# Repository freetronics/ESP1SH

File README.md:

Freetronics ESP8266 / ESP-01 (WiFi) Breakout Shield
===================================================
Copyright 2014-2017 Freetronics Pty Ltd www.freetronics.com  

A shield for the Arduino and other microcontroller boards based on the
same header format, such as the Freetronics Eleven. Includes a header
to mount an ESP-01 module containing an ESP8266 WiFi chipset and
supporting parts, giving your Arduino WiFi capabilities.

Includes level shifters to allow safe operation on both 3.3V and 5V
Arduino boards.

More information is available on our product page at:

  http://www.freetronics.com/esp1sh

http://tminusarduino.blogspot.com.au/2014/09/experimenting-with-esp8266-5-wifi-module.html

INSTALLATION
------------
The design is saved as an EAGLE project. EAGLE PCB design software is
available from www.cadsoftusa.com free for non-commercial use. To use
this project download it and place the directory containing these files
into the "eagle" directory on your computer. Then open EAGLE and
navigate to the project.

DISTRIBUTION
------------
The specific terms of distribution of this project are governed by the
license referenced below.

LICENSE
-------
Licensed under the TAPR Open Hardware License (www.tapr.org/OHL).
The "license" folder within this repository also contains a copy of
this license in plain text format.

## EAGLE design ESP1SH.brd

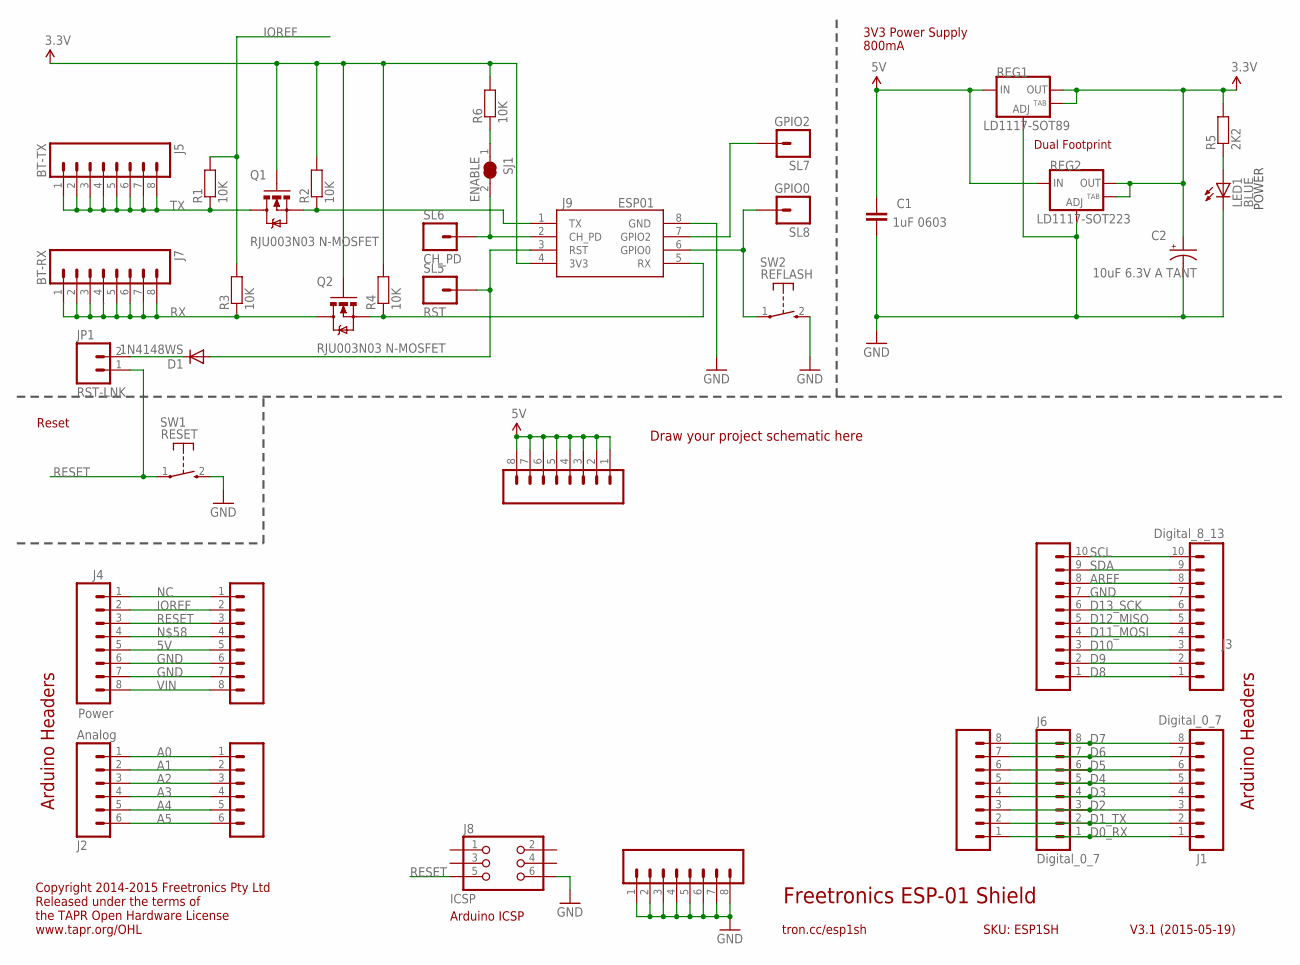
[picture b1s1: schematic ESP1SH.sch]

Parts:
C1: 1uF 0603; 0603
C2: 10uF 6.3V A TANT; EIA3216
D1: 1N4148WS; SOD-323
J1, J6: Digital_0_7; 1X08
J2: Analog; 1X06
J3: Digital_8_13; 1X10
J4: Power; 1X08
J5: BT-TX; 1X08
J7: BT-RX; 1X08
J8: ICSP; 2X03PTH
J9: ESP01
JP1: RST-LNK; 1X02
LED1: BLUE; LED-0603
Q1, Q2: RJU003N03 N-MOSFET; SOT32-3
R1, R2, R3, R4, R6: 10K; 0603
R5: 2K2; 0603
REG1: LD1117-SOT89; SOT89
REG2: LD1117-SOT223; SOT223
SJ1: ENABLE; SJC
SL1: Digital_0_7; 1X08
SL2: Analog; 1X06
SL3: Digital_8_13; 1X10
SL4: Power; 1X08
SL5: RST; 1X01
SL6: CH_PD; 1X01
SL7: GPIO2; 1X01
SL8: GPIO0; 1X01
SL9: GND; 1X08
SL10: 5V; 1X08
SW1: RESET; TACTILE_SWITCH_SMD_2PIN_TINY
SW2: REFLASH; TACTILE_SWITCH_SMD_2PIN_TINY

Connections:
3.3V: C2.A (+), J9.4 (3V3), Q1.1 (G), Q2.1 (G), R2.2, R4.2, R5.2, R6.2, REG1.2 (OUT), REG1.4 (OUT), REG2.2 (OUT), REG2.4 (OUT)
5V: C1.1, J4.5, REG1.3 (IN), REG2.3 (IN), SL4.5, SL10.1, SL10.2, SL10.3, SL10.4, SL10.5, SL10.6, SL10.7, SL10.8
A0: J2.1, SL2.1
A1: J2.2, SL2.2
A2: J2.3, SL2.3
A3: J2.4, SL2.4
A4: J2.5, SL2.5
A5: J2.6, SL2.6
AREF: J3.8, SL3.8
D0_RX: J1.1, J6.1, SL1.1
D1_TX: J1.2, J6.2, SL1.2
D2: J1.3, J6.3, SL1.3
D3: J1.4, J6.4, SL1.4
D4: J1.5, J6.5, SL1.5
D5: J1.6, J6.6, SL1.6
D6: J1.7, J6.7, SL1.7
D7: J1.8, J6.8, SL1.8
D8: J3.1, SL3.1
D9: J3.2, SL3.2
D10: J3.3, SL3.3
D11_MOSI: J3.4, SL3.4
D12_MISO: J3.5, SL3.5
D13_SCK: J3.6, SL3.6
GND: C1.2, C2.C (-), J3.7, J4.6, J4.7, J8.6, J9.8 (GND), LED1.C, REG1.1 (ADJ), REG2.1 (ADJ), SL3.7, SL4.6, SL4.7, SL9.1, SL9.2, SL9.3, SL9.4, SL9.5, SL9.6, SL9.7, SL9.8, SW1.2 (S), SW2.2 (S)
IOREF: J4.2, R1.2, R3.2, SL4.2
unnamed: J9.6 (GPIO0), SL8.1, SW2.1
unnamed: J9.7 (GPIO2), SL7.1
unnamed: D1.2 (A), J9.3 (RST), SL5.1
unnamed: J9.2 (CH_PD), SJ1.2, SL6.1
unnamed: LED1.A, R5.1
unnamed: J9.1 (TX), Q1.2 (S), R2.1
unnamed: J9.5 (RX), Q2.2 (S), R4.1
unnamed: J4.4, SL4.4
unnamed: R6.1, SJ1.1
unnamed: D1.1 (C), JP1.2
NC: J4.1, SL4.1
RESET: J4.3, J8.5, JP1.1, SL4.3, SW1.1
RX: J7.1, J7.2, J7.3, J7.4, J7.5, J7.6, J7.7, J7.8, Q2.3 (D), R3.1
SCL: J3.10, SL3.10
SDA: J3.9, SL3.9
TX: J5.1, J5.2, J5.3, J5.4, J5.5, J5.6, J5.7, J5.8, Q1.3 (D), R1.1
VIN: J4.8, SL4.8

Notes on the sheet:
Freetronics ESP-01 Shield
V3.1 (2015-05-19)
tron.cc/esp1sh
SKU: ESP1SH
Arduino Headers
Reset
Draw your project schematic here
Arduino ICSP
Copyright 2014-2015 Freetronics Pty Ltd Released under the terms of the TAPR Open Hardware License www.tapr.org/OHL
POWER
3V3 Power Supply
Dual Footprint
800mA

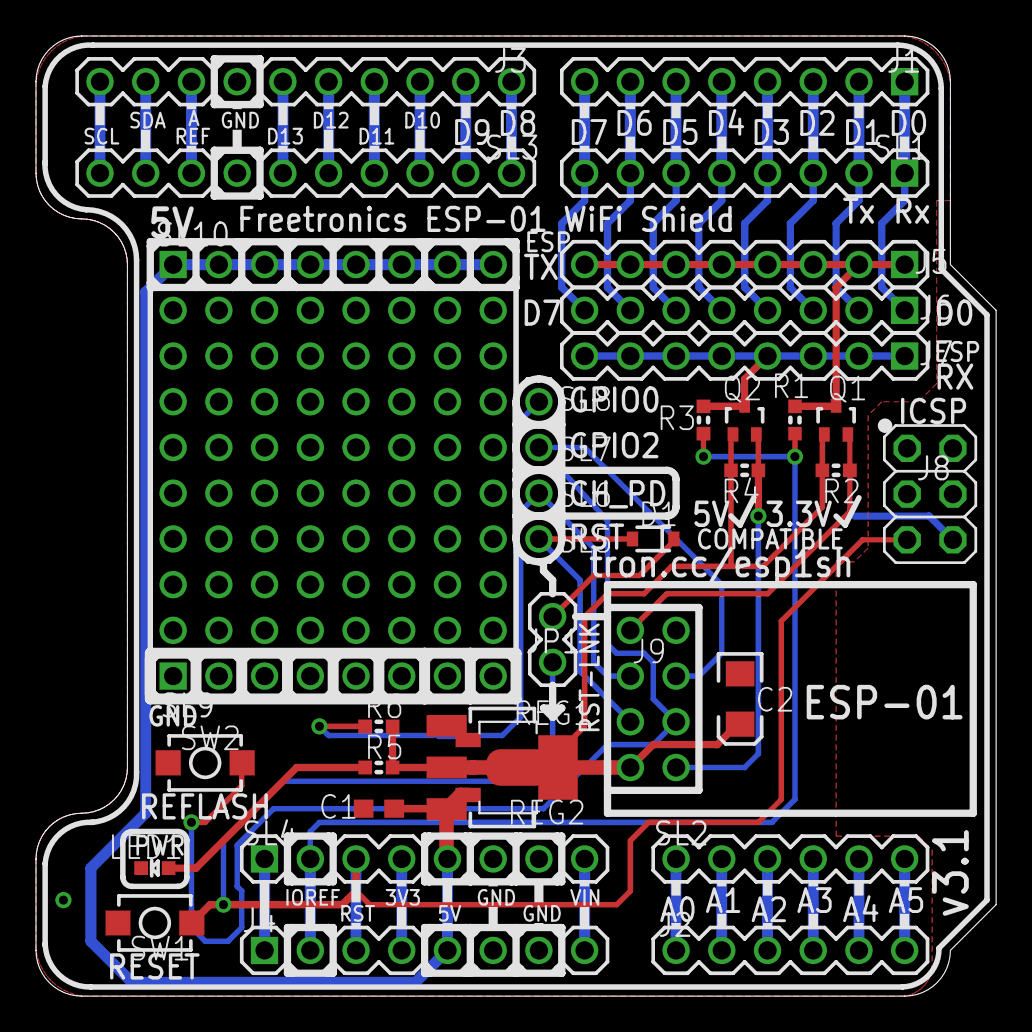
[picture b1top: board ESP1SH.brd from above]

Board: 2 copper layers, 53.3 x 53.3 mm, 37 parts (1 on the bottom side), 42 nets.

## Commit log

2014-11-19 Version 1.0 release
2015-02-05 Added onboard voltage regulator for v1.1 release
2015-03-15 Add schematic PDF
2015-05-19 Added REFLASH button connected to CH_PD
2015-05-19 Changed REFLASH button from CH_PD to GPIO0
2018-03-28 Board updates for v3.1 release

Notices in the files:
ESP1SH.brd:
(c) 2015 Freetronics Pty Ltd
Open Hardware License
